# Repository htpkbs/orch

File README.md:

# Overview

The orch is a keyboard PCB.

It has:

* A mostly ortholinear layout
* Key sizes that fit most GMK keycap sets
* 1.25u super/meta/command keys
* 19mm switch spacing
* An arrow key cluster
* A function key column
* USB-C
* A rotary encoder
* No stabilizers unless you want one for a 2U spacebar
* Optional 2U spacebar or 2 1U keys

# Key Layout

The key layout looks like this. (Thanks to [Keyboard Layout Editor](http://www.keyboard-layout-editor.com/) for the image.)

This is the corresponding data for pasting into Keyboard Layout Editor:

```
[{x:0.25,c:"#393b3b",t:"#9065c7",a:6,w:1.5},"Tab",{c:"#727474",t:"#c6c9c7",a:4,f:5},"Q","W","E","R","T","Y","U","I","O","P","{\n[","}\n]",{w:1.5},"|\n\\",{c:"#393b3b",x:0.25,t:"#c6c9c7",a:4,f:3},"Page\n\n\n\n\n\nUp"],
[{t:"#689b34",a:6,w:1.75},"Control",{c:"#727474",t:"#c6c9c7",a:4,f:5},"A","S","D","F","G","H","J","K","L",":\n;","\"\n'",{c:"#393b3b",t:"#689b34",a:6,f:3,w:1.75},"Function",{x:1,t:"#c6c9c7",a:4},"Page\n\n\n\n\n\nDown"],
[{t:"#ee6d00",a:6,w:1.75},"Shift",{c:"#727474",t:"#c6c9c7",a:4,f:5},"Z","X","C","V","B","N","M","<\n,",">\n.","?\n/",{c:"#393b3b",t:"#ee6d00",a:6,f:3,w:1.25},"Shift",{x:2.5,t:"#dd1126"},"Code"],
[{y:-0.75,x:13.25,t:"#c6c9c7",a:4,f:5},"&uarr;"],
[{y:-0.25,x:0.5,t:"#ee6d00",a:6,f:3},"Fn",{t:"#0084c2"},"Ctrl","Alt",{t:"#dd1126",w:1.25},"Code",{t:"#0084c2"},"Code",{c:"#727474",t:"#000000",a:7},"","",{c:"#393b3b",t:"#0084c2",a:6},"Code",{t:"#dd1126",w:1.25},"Code",{t:"#0084c2"},"Alt","Ctrl",{x:3.5,t:"#dd1126"},"Code"],
[{y:-0.75,x:12.25,t:"#c6c9c7",a:4,f:5},"&larr;","&darr;","&rarr;"]
```

# PCB Renders

# Case

[Case files are in the case directory](case) and include a cutout for the rotary encoder. The "closed" layer requires some dremeling or filing to make room for the USB connector. Thanks to the [swillkb Plate & Case Builder](http://builder.swillkb.com/). There are two bottom case files included. One of them has smaller holes that are meant for tapping (to secure the screws directly into the back case layer), and the other has "open" holes that an M2 screw will fit through (to secure the case together with nuts).

# Schematic

[There is a PDF of the schematic here](assets/schematic.pdf).

# AVR Notes

These are just some notes on programming the ATmega32U4. [The datasheet is here](http://ww1.microchip.com/downloads/en/DeviceDoc/Atmel-7766-8-bit-AVR-ATmega16U4-32U4_Datasheet.pdf).

## Programming

ISP headers are included in the "No Legs" Tag-Connect format. You need a Tag-Connect cable and retaining clip board to connect to it. For example, if you have an AVRISP mkII programmer, you need the ["No Legs" cable](https://www.tag-connect.com/product/tc2030-idc-nl) and the [retaining clip board](https://www.tag-connect.com/product/tc2030-retaining-clip-board-3-pack).

## Fuses

Default values are:

```
E:F3, H:99, L:5E
```

### Extended

| Name | Bit | Value | Status | Reason |
| --- | --- | --- | --- | --- |
| - | 7 | 1 | Unprogrammed | Unused |
| - | 6 | 1 | Unprogrammed | Unused |
| - | 5 | 1 | Unprogrammed | Unused |
| - | 4 | 1 | Unprogrammed | Unused |
| HWBE | 3 | 0 | Programmed | Pin used to force bootloader after reset |
| BODLEVEL2 | 2 | 0 | Programmed | 4.3V brown-out reset threshold |
| BODLEVEL1 | 1 | 0 | Programmed | 4.3V brown-out reset threshold |
| BODLEVEL0 | 0 | 0 | Programmed | 4.3V brown-out reset threshold |

Hex value is `F0`.

### High

| Name | Bit | Value | Status | Reason |
| --- | --- | --- | --- | --- |
| OCDEN | 7 | 1 | Unprogrammed | OCD disabled |
| JTAGEN | 6 | 0 | Programmed | JTAG enabled |
| SPIEN | 5 | 0 | Programmed | SPI enabled |
| WDTON | 4 | 1 | Unprogrammed | Watchdog timer in interrupt mode |
| EESAVE | 3 | 1 | Unprogrammed | EEPROM preserved on chip erase |
| BOOTSZ1 | 2 | 0 | Programmed | Default maximum boot size |
| BOOTSZ0 | 1 | 0 | Programmed | Default maximum boot size |
| BOOTRST | 0 | 1 | Unprogrammed | 4.3V brown-out reset threshold |

Hex value is `99`.

### Low

| Name | Bit | Value | Status | Reason |
| --- | --- | --- | --- | --- |
| CKDIV8 | 7 | 1 | Unprogrammed | Don't divide clock by 8 |
| CKOUT | 6 | 1 | Unprogrammed | Don't output clock |
| SUT1 | 5 | 0 | Programmed | Crystal oscillator with BOD enabled |
| SUT0 | 4 | 1 | Unprogrammed | Crystal oscillator with BOD enabled |
| CKSEL3 | 3 | 1 | Unprogrammed | Low power 16MHz crystal oscillator |
| CKSEL2 | 2 | 1 | Unprogrammed | Low power 16MHz crystal oscillator |
| CKSEL1 | 1 | 1 | Unprogrammed | Low power 16MHz crystal oscillator |
| CKSEL0 | 0 | 1 | Unprogrammed | Crystal oscillator with BOD enabled |

Hex value is `DD`.

### Setting Fuse Values

avrdude commands to set the fuse values with an AVRISP mkII programmer:

```
avrdude -p m32u4 -c avrispmkII -U efuse:w:0xF0:m
avrdude -p m32u4 -c avrispmkII -U hfuse:w:0x99:m
avrdude -p m32u4 -c avrispmkII -U lfuse:w:0xDD:m
```

Note that the extended fuse will always show as `C0` with avrdude (despite the datasheet saying that the first four bits are unprogrammed/`1111`).

You may need to erase the chip before you set the fuse values:

```
avrdude -p m32u4 -c avrispmkII -e
```

The first time flashing should be done with a programmer like the AVRISP mkII and you should compile QMK to include the bootloader in the firmware file (using `:production`). I have [a fork of the `qmk_firmware` repository here](https://github.com/htpkbs/qmk_firmware/tree/orch) that I may or may not try to get merged at some point.) To compile the `orch` branch with the QMK CLI:

```
qmk compile -kb orch -km default:production
```

I've had luck setting a custom bitclock setting (`-B`) for the initial flash when using the mkII, but this may not matter. For example:

```
avrdude -p m32u4 -c avrispmkII -U flash:w:orch_default_production.hex:i -B 154.37
```

You should now be able to flash regular (non-`:production`) firmware that doesn't include the bootloader over USB using QMK Tookbox.

# Sublicenses

* Thank you to [coseyfannitutti](https://github.com/coseyfannitutti) for the footprints `D_DO-35_SOD27_P5.08mm_Horizontal.kicad_mod` and `USB_C_GCT_USB4085.kicad_mod`. [The Creative Commons license for these is included here](LICENSE.CFTKB).
* Thanks to [ai03-2725](https://github.com/ai03-2725) for the `MX*` symbols. [The MIT license for these is included here](LICENSE.ai03).

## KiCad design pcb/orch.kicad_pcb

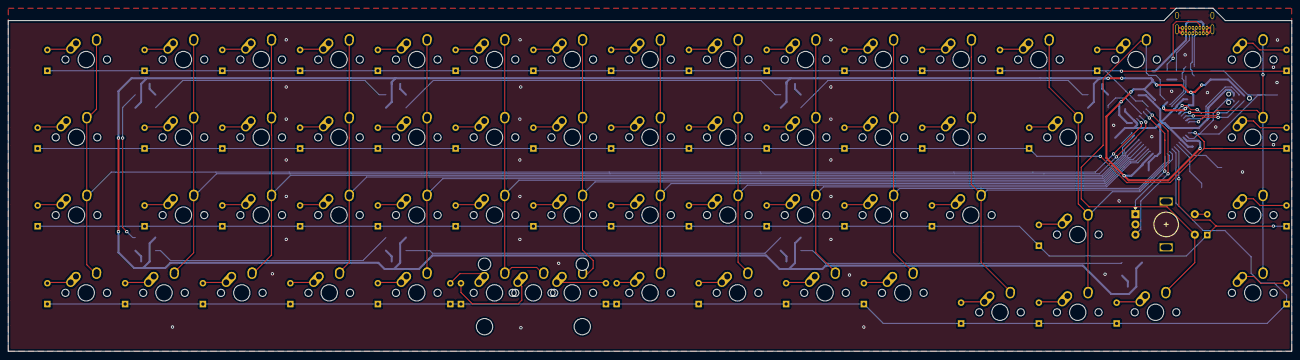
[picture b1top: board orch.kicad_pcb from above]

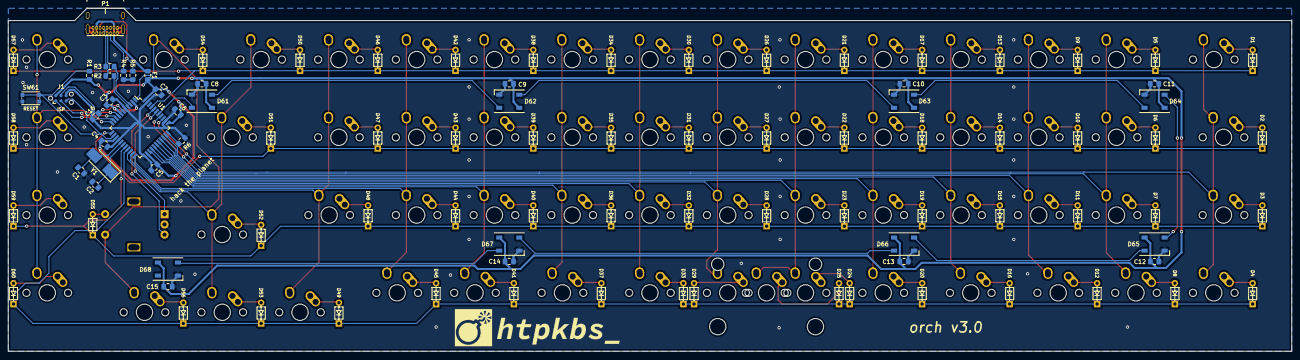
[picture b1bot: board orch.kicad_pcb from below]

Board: 2 copper layers, 313.6 x 83.8 mm, 156 parts (96 on the bottom side), 106 nets.

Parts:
C1, C2: 22pF; C_0805_2012Metric_Pad1.18x1.45mm_HandSolder
C3: 4.7u; C_0805_2012Metric_Pad1.18x1.45mm_HandSolder
C4, C5, C6, C7, C8, C9, C10, C11, C12, C13, C14, C15: 0.1u; C_0805_2012Metric_Pad1.18x1.45mm_HandSolder
C16: 1u; C_0805_2012Metric_Pad1.18x1.45mm_HandSolder
D1, D2, D3, D4, D5, D6, D7, D8, D9, D10, D11, D12, D13, D14, D15, D16, D17, D18, D19, D20, D21, D22, D23, D24, D25, D26, D27, D28, D29, D30, D31, D32, D33, D34, D35, D36, D37, D38, D39, D40, D41, D42, D43, D44, D45, D46, D47, D48, D49, D50, D51, D52, D53, D54, D55, D56, D57, D58, D59, D60: 1N4148; D_DO-35_SOD27_P5.08mm_Horizontal
D61, D62, D63, D64, D65, D66, D67, D68: SK6812; LED_SK6812_PLCC4_5.0x5.0mm_P3.2mm
F1: 100mA; Fuse_0805_2012Metric_Pad1.15x1.40mm_HandSolder
J1: AVR-ISP-6; Tag-Connect_TC2030-IDC-NL_2x03_P1.27mm_Vertical
P1: USB_C_Receptacle_USB2.0; USB_C_GCT_USB4085
R1: 10k; R_0805_2012Metric_Pad1.15x1.40mm_HandSolder
R2, R3: 22R; R_0805_2012Metric_Pad1.15x1.40mm_HandSolder
R4, R5: 5.1k; R_0805_2012Metric_Pad1.15x1.40mm_HandSolder
R6: 10K; R_0805_2012Metric_Pad1.15x1.40mm_HandSolder
SW1, SW54: MX-NoLED; MX-1.5U-NoLED
SW2, SW3, SW51: MX-NoLED; MX-1.75U-NoLED
SW4, SW5, SW6, SW7, SW8, SW9, SW10, SW11, SW12, SW13, SW14, SW15, SW17, SW18, SW19, SW20, SW21, SW22, SW23, SW24, SW26, SW27, SW28, SW29, SW30, SW31, SW32, SW33, SW34, SW35, SW36, SW38, SW39, SW40, SW41, SW42, SW43, SW44, SW45, SW46, SW47, SW49, SW50, SW52, SW53, SW56, SW57, SW58, SW59, SW60: MX-NoLED; MX-1U-NoLED
SW16, SW37, SW48: MX-NoLED; MX-1.25U-NoLED
SW25: MX-NoLED; MX-2U-NoLED
SW55: Rotary_Encoder_Switch; RotaryEncoder_Alps_EC11E-Switch_Vertical_H20mm
SW61: Reset; SW_Push_1P1T_NO_CK_KMR2
U1: ATmega32U4-AU; TQFP-44_10x10mm_P0.8mm
Y1: 16MHz; Crystal_SMD_Abracon_ABM3-2Pin_5.0x3.2mm_HandSoldering

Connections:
+5V: C3.2, C4.2, C5.2, C6.2, C7.2, C8.1, C9.1, C10.1, C11.1, C12.1, C13.1, C14.1, C15.1, D61.3, D62.3, D63.3, D64.3, D65.3, D66.3, D67.3, D68.3, F1.1, J1.2, R1.1, U1.2, U1.7, U1.14, U1.24, U1.34, U1.44
/Col1: SW1.2, SW2.2, SW3.2, SW4.2, U1.36
/Col2: SW5.2, SW6.2, SW7.2, SW8.2, U1.37
/Col3: SW9.2, SW10.2, SW11.2, SW12.2, U1.32
/Col4: SW13.2, SW14.2, SW15.2, SW16.2, U1.31
/Col5: SW17.2, SW18.2, SW19.2, SW20.2, U1.30
/Col6: SW21.2, SW22.2, SW23.2, SW24.2, SW25.2, U1.29
/Col7: SW26.2, SW27.2, SW28.2, SW29.2, U1.28
/Col8: SW30.2, SW31.2, SW32.2, SW33.2, U1.27
/Col9: SW34.2, SW35.2, SW36.2, SW37.2, U1.26
/Col10: SW38.2, SW39.2, SW40.2, SW41.2, U1.25
/Col11: SW42.2, SW43.2, SW44.2, SW45.2, U1.22
/Col12: SW46.2, SW47.2, SW48.2, SW49.2, U1.21
/Col13: SW50.2, SW51.2, SW52.2, SW53.2, U1.20
/Col14: SW54.2, SW55.S1, SW56.2, U1.1
/Col15: SW57.2, SW58.2, SW59.2, SW60.2, U1.8
/D+: R2.1, U1.4
/D-: R3.1, U1.3
/MISO: J1.1, U1.11
/MOSI: J1.4, U1.10
/RGB: D61.2, U1.38
/Reset: J1.5, R1.2, SW61.1, U1.13
/RotaryA: SW55.A, U1.39
/RotaryB: SW55.B, U1.40
/Row1: D1.1, D5.1, D9.1, D13.1, D17.1, D21.1, D26.1, D30.1, D34.1, D38.1, D42.1, D46.1, D50.1, D54.1, D57.1, U1.41
/Row2: D2.1, D6.1, D10.1, D14.1, D18.1, D22.1, D27.1, D31.1, D35.1, D39.1, D43.1, D47.1, D51.1, D58.1, U1.12
/Row3: D3.1, D7.1, D11.1, D15.1, D19.1, D23.1, D28.1, D32.1, D36.1, D40.1, D44.1, D48.1, D52.1, D55.1, D59.1, U1.18
/Row4: D4.1, D8.1, D12.1, D16.1, D20.1, D24.1, D25.1, D29.1, D33.1, D37.1, D41.1, D45.1, D49.1, D53.1, D56.1, D60.1, U1.19
/SCK: J1.3, U1.9
/USB_D+: P1.A6, P1.B6, R2.2
/USB_D-: P1.A7, P1.B7, R3.2
/XTAL1: C2.2, U1.17, Y1.1
/XTAL2: C1.2, U1.16, Y1.2
GND: C1.1, C2.1, C3.1, C4.1, C5.1, C6.1, C7.1, C8.2, C9.2, C10.2, C11.2, C12.2, C13.2, C14.2, C15.2, C16.2, D61.1, D62.1, D63.1, D64.1, D65.1, D66.1, D67.1, D68.1, J1.6, P1.A1, P1.A12, P1.B1, P1.B12, P1.S1, R4.1, R5.1, R6.1, SW55.C, SW61.2, U1.5, U1.15, U1.23, U1.35, U1.43
unnamed: C16.1, U1.6
unnamed: D1.2, SW1.1
unnamed: D2.2, SW2.1
unnamed: D3.2, SW3.1
unnamed: D4.2, SW4.1
unnamed: D5.2, SW5.1
unnamed: D6.2, SW6.1
unnamed: D7.2, SW7.1
unnamed: D8.2, SW8.1
unnamed: D9.2, SW9.1
unnamed: D10.2, SW10.1
unnamed: D11.2, SW11.1
unnamed: D12.2, SW12.1
unnamed: D13.2, SW13.1
unnamed: D14.2, SW14.1
unnamed: D15.2, SW15.1
unnamed: D16.2, SW16.1
unnamed: D17.2, SW17.1
unnamed: D18.2, SW18.1
unnamed: D19.2, SW19.1
unnamed: D20.2, SW20.1
unnamed: D21.2, SW21.1
unnamed: D22.2, SW22.1
unnamed: D23.2, SW23.1
unnamed: D24.2, SW24.1
unnamed: D25.2, SW25.1
unnamed: D26.2, SW26.1
unnamed: D27.2, SW27.1
unnamed: D28.2, SW28.1
unnamed: D29.2, SW29.1
unnamed: D30.2, SW30.1
unnamed: D31.2, SW31.1
unnamed: D32.2, SW32.1
unnamed: D33.2, SW33.1
unnamed: D34.2, SW34.1
unnamed: D35.2, SW35.1
unnamed: D36.2, SW36.1
unnamed: D37.2, SW37.1
unnamed: D38.2, SW38.1
unnamed: D39.2, SW39.1
unnamed: D40.2, SW40.1
unnamed: D41.2, SW41.1
unnamed: D42.2, SW42.1
unnamed: D43.2, SW43.1
unnamed: D44.2, SW44.1
unnamed: D45.2, SW45.1
unnamed: D46.2, SW46.1
unnamed: D47.2, SW47.1
unnamed: D48.2, SW48.1
unnamed: D49.2, SW49.1
unnamed: D50.2, SW50.1
unnamed: D51.2, SW51.1
unnamed: D52.2, SW52.1
unnamed: D53.2, SW53.1
unnamed: D54.2, SW54.1
unnamed: D55.2, SW55.S2
unnamed: D56.2, SW56.1
unnamed: D57.2, SW57.1
unnamed: D58.2, SW58.1
unnamed: D59.2, SW59.1
unnamed: D60.2, SW60.1
unnamed: D61.4, D62.2
unnamed: D62.4, D63.2
unnamed: D63.4, D64.2
unnamed: D64.4, D65.2
unnamed: D65.4, D66.2
unnamed: D66.4, D67.2
unnamed: D67.4, D68.2
unnamed: F1.2, P1.A4, P1.A9, P1.B4, P1.B9
unnamed: P1.A5, R4.2
unnamed: P1.B5, R5.2
unnamed: R6.2, U1.33

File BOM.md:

# Bill of Materials

J1 (the Tag-Connect ISP headers) and SW1-SW60 (the key switches) are not included.

| Reference | Quantity | Value | Link |
| --- | --- | --- | --- |
| C1, C2 | 2 | 22pF | https://www.digikey.com/en/products/detail/avx-corporation/0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 |
| C3 | 1 | 4.7u | https://www.digikey.com/en/products/detail/avx-corporation/0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 |
| C4-C13 | 4 | 0.1u | https://www.digikey.com/en/products/detail/avx-corporation/0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 |
| C14 | 1 | 1u | https://www.digikey.com/en/products/detail/avx-corporation/0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 |
| D1-D60 | 60 | 1N4148 | https://www.digikey.com/product-detail/en/vishay-semiconduct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 |
| D61-D66 | 6 | SK6812 | https://www.digikey.com/en/products/detail/adafruit-industri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 |
| F1 | 1 | 100mA | https://www.digikey.com/en/products/detail/littelfuse-inc/08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 |
| P1 | 1 | USB_C_Receptacle_USB2.0 | https://www.digikey.com/product-detail/en/USB4085-GF-A/2073-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 |
| R1, R6 | 2 | 10k | https://www.digikey.com/en/products/detail/bourns-inc/CR0805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 |
| R2, R3 | 2 | 22R | https://www.digikey.com/en/products/detail/bourns-inc/CR0805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 |
| R4, R5 | 2 | 5.1k | https://www.digikey.com/en/products/detail/bourns-inc/CR0805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 |
| SW61 | 1 | Reset | https://www.digikey.com/en/products/detail/c-k/KMR241NG-LFS/2176486 |
| U1 | 1 | ATmega32U4-AU | https://www.digikey.com/en/products/detail/microchip-technol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 |
| Y1 | 1 | 16MHz | https://www.digikey.com/en/products/detail/abracon-llc/ABM3-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 |

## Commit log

2021-01-15 pcb layout
2021-01-15 pcb done
2021-01-16 v0.0.1
2021-01-16 images
2021-01-16 fix images
2021-01-16 licenses
2021-01-16 clean up pages
2021-01-16 better renders
2021-01-17 schematic
2021-01-17 readme
2021-01-19 logo
2021-01-19 new logos
2021-01-20 move logos
2021-01-26 add fuses
2021-01-26 tag-connect
2021-01-26 fix avrdude part number
2021-01-28 fix rows and start new traces
2021-01-29 v1.0.0
2021-01-29 chip erase and efuse notes
2021-01-29 formatting
2021-02-02 rotary encoder?
2021-02-02 redo power
2021-02-08 add isp label
2021-02-08 add case files
2021-02-08 rotary encoder on layout
2021-02-08 outline
2021-02-08 swillkb
2021-02-08 some new case things, updated BOM
2021-02-08 fix typo in bom
2021-02-09 routing is somewhat better now
2021-02-09 better link
2021-02-12 fix caps for leds
2021-02-12 update schematic and renders
2021-02-16 v2.1 - add caps to LEDs, re-do some routing
2021-02-16 update bom, renumber caps
2021-02-18 bump out usb connector
2021-02-23 some changes
2021-05-11 unused footprint
2021-05-11 + wip
2021-05-11 re-add LEDs
2021-08-21 Fix key
2021-08-21 flip usb
2021-08-21 flip
2021-09-06 Move case files around, update README
2021-09-06 Add a space
2021-09-09 Fix version in README

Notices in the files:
pcb/orch.kicad_pcb:
License: BSD 2-Clause
